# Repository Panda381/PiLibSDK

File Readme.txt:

PiLibSDK - Raspberry Pi bare-metal SDK library
==============================================
Pre-alpha version 0.46, in progress - under development
Last update: 08/05/2026

Copyright (c) 2026 Miroslav Nemecek

Panda38@seznam.cz
hardyplotter2@gmail.com
https://github.com/Panda381/PiLibSDK
https://www.breatharian.eu/hw/pilibsdk/index_en.html

License
=======
All of my software creations are distributed under the Unlicense
https://spdx.org/licenses/Unlicense.html,
and my hardware creations under the CC0 license
https://creativecommons.org/publicdomain/zero/1.0/legalcode.en.
You are free to use, modify, and distribute them for any purpose without having
to credit me as the author. The exception is content derived from third-party
sources. These third-party components are not covered by my Unlicense or CC0
licenses, but rather by the original license terms of their authors. These
components are marked in the code, and when using them, you must comply with
the terms of the original licenses.

All of my source code and data are completely free to use for any purpose. The
exception is certain files derived from third-party sources - these are subject
to the original author's license. This includes most fonts, as well as portions
of source files taken from the Circle library and Linux code - these sections
are marked in the source files.

Most fonts in this library are not my creation. They were downloaded from the
internet from unknown sources, with unknown license terms of use. If you want
to use only strict licenses, do not use fonts from this library.

Intro
=====
PiLibSDK is a bare-metal library for Raspberry Pi modules. "Bare-metal" means
that programs run directly on the hardware without an operating system, they
are not controlled by the operating system, and they have full access to the
hardware. Raspberry Pi modules can thus be used in a similar way to microchips.
Another advantage is that the device is fully operational within 3 seconds of
powering on. Currently, the Raspberry Zero 1, Zero 2 W, Pi 2, and Pi 3 modules
are supported. Support for the Pi 4 and Pi 5 modules is very limited, and they
will likely not be supported in the future either, as their benefits for
bare-metal use are minimal.

Sample programs have been prepared for the BarePi modular microchip kit.
(links: https://www.breatharian.eu/hw/barepi/index_en.html,
https://github.com/Panda381/BarePi). Of course, you don't have to follow the
hardware wiring exactly, but this is the most common pin-to-signal mapping.
The main device is the ZeroTiny game console, which corresponds to the
configuration of the "Zero," "Base," and "KeyPad" modules.

An LCD SPI display with a resolution of 320x240 pixels and ST7789 controller
can also be connected to the device. The wiring corresponds to the
"LCD320x240" module from the BarePi kit. The software library is designed so
that when it detects the connection of the LCD320x240 module, it activates the
SPI output to the display and sends the image to this LCD display as well.
Detection is performed using a 10K resistor connected between the DC and CS
pins. If you want to be able to disable the LCD display output on the target
device, you can do so using a switch that connects this 10K resistor. Detection
occurs when the application or loader starts - so after changing the switch,
you must terminate or start the program or loader. Disabling the output to the
LCD display ensures faster program execution, as sending data to the LCD
display heavily loads the program.

Although the LCD SPI display has a resolution of only 320x240 pixels, it is
possible to use programs with a resolution of 640x480 pixels. The driver
automatically scales the image down to the target size. If you need to display
details on the LCD display that would be lost due to the scaling, you can do so
by pressing Alt+[A] - the "Insert" function is used here to mean "Zoom". When
you press the keys, the LCD display will sequentially show each of the four
quadrants of the image in full resolution; pressing the keys a fifth time
restores the full scaled-down image.

If you do not need the HDMI output while using the LCD display, disconnect the
monitor cable. This will result in a significant reduction in current
consumption (from approximately 400 mA to 200 mA), which is especially
important when running the console on battery power. The system detects whether
an HDMI monitor is connected when the program starts - therefore, after
disconnecting or connecting an HDMI monitor, you must exit or restart the
program or loader. With the Raspberry Zero 1 module, it may be necessary to
disconnect and reconnect the power supply to detect the HDMI monitor.

If you connect a DS3231 real-time clock circuit to the device, applications
will retrieve the current real-time clock value from it. The I2C EEPROM memory
provides the ability to save program configurations.

A boot loader is available for BarePi devices, which allows easy launching of
programs from an SD card. The programs are ready for BarePi and ZeroTiny with
Zero 1, Zero 2 32-bit, or Zero 2 64-bit modules. The Zero 1 and Zero 2 modules
differ primarily in speed - the Zero 2 is noticeably faster than the Zero 1.
The higher speed is due not only to a higher processor frequency but also to a
newer architecture. In addition, the Zero 2 module has 4 cores, while the
Zero 1 has only one core. Therefore, it is strongly recommended to use the
Zero 2 module. Use the Zero 1 module only if you own it and have no better use
for it. The Zero 2 module can be operated in 32-bit or 64-bit mode. 64-bit mode
is faster. The compilations are prepared for both modes. From a user's point of
view, there is no noticeable difference between the modes. It is recommended to
prefer 64-bit mode, which may be slightly faster in some cases.

The BarePi kit can be controlled using either the "KeyPad" gaming keyboard or
the "MiniKey" alphanumeric keyboard. The keys on the "KeyPad" keyboard are also
mapped to the keys on the "MiniKey" keyboard. To distinguish between key
labels, action keys from the gaming keyboard are listed in square brackets,
while character keys are listed without brackets. For example, "[A]" denotes
the "A" action key on the gaming keyboard. The meanings of the keys on the
gaming keyboard and their mapping to the alphanumeric keyboard are as follows.

[A] = Space ... Main action button
[B] = Enter ... Secondary action button
[X] = Tab ... Auxiliary button, e.g. Help
[Y] = Esc ... Exit the menu, close the program
Alt+Left = Home ... Jump to start
Alt+Right = End ... Jump to end
Alt+Up = PgUp ... Page up
Alt+Down = PgDn ... Page down
Alt+A = Insert ... Insert mode (on LCD display, the "Zoom" function)
Alt+B = Edit ... Edit mode
Alt+X = PrtScr ... Take a screenshot and save it to an SD card
Alt+Y = Menu ... Call system menu

Note: A boot loader is not required to run programs. You can run programs
directly on the Zero1/Zero2 module itself, without additional hardware or a
boot loader. Copy the system files from the Root directory of the corresponding
!BarePi* folder to the SD card. You will need the files "bootcode.bin",
"config.txt", "fixup.dat", and "start.elf". Copy the program to the Root folder
as well, and rename it to KERNEL.IMG. The program will start automatically when
power is turned on.

Compilation
===========
To compile 32-bit mode, you will need AArch32 GCC
(tool name "arm-none-eabi"). Install to C:\ARM_GCC32.
https://developer.arm.com/-/media/Files/downloads/gnu/15.2.rel1/binrel/arm-gnu-toolchain-15.2.rel1-mingw-w64-i686-arm-none-eabi.msi

To compile 64-bit mode, you will need AArch64 GCC
(tool name "aarch64-none-elf"). Install to C:\ARM_GCC64.
 https://developer.arm.com/-/media/Files/downloads/gnu/15.2.rel1/binrel/arm-gnu-toolchain-15.2.rel1-mingw-w64-i686-aarch64-none-elf.msi
from https://developer.arm.com/downloads/-/arm-gnu-toolchain-downloads

If you will use another paths, edit paths in _c1.bat (set GCC_PI_PATH).

Directories
===========
!BarePi ... content of SD card for kit BarePi and ZeroTiny - common files
!BarePi_1 ... content of SD card for kit BarePi and ZeroTiny - executables for module Zero 1
!BarePi_3 ... content of SD card for kit BarePi and ZeroTiny - executables for module Zero 2 32-bit
!BarePi_4 ... content of SD card for kit BarePi and ZeroTiny - executables for module Zero 2 64-bit
_devices ... devices: BarePi = modular microchip kit and ZeroTiny device
_drv ... drivers
_font ... fonts
_lib ... libraries
_sdk ... SDK (peripheral controllers)
_tools ... compilation tools
Apps ... source codes of sample applications

To prepare the SD card, format it to FAT32, copy the contents of the !BarePi
folder to it, as well as one of the !BarePi_* folder (depending on the module
type).

Order of includes:

-> project "include.h"
   -> root "includes.h" (INCLUDES_H)
       -> root "global.h"
          -> project "config.h"
             -> root "config_def.h" (CONFIG_DEF_H)
                -> (called from start of config_def.h) device "_devices/barepi/_config.h"
       -> fonts "_font/_include.h"
       -> SDK "_sdk/_include.h"
       -> drivers "_drv/_include.h"
       -> LIB "_lib/_include.h"
       -> device "_devices/barepi/_include.h"

ZeroTiny
========
ZeroTiny is the simplest game console based on the Raspberry Pi Zero 1 or
Zero 2 modules. This corresponds to the assembly of the "Zero," "Base," and
"KeyPad" modules from the BarePi kit. It is recommended to preferably use the
Zero 2 module in 64-bit mode. The Zero 1 module may be noticeably slower in
some applications. ZeroTiny features 9 buttons, a stereo PWM audio output, and
an HDMI display output. A boot loader is available, allowing for easy program
launch from an SD card.

The ZeroTiny is designed in a sandwich-style construction. In my prototype,
I connected the Zero module to the motherboard via an 8mm header - primarily to
facilitate easy module replacement. If you solder the Zero module to the board
using only a pin header, the design will be lower. However, this may make
repairs more difficult, such as replacing a button.

Detailed materials for ZeroTiny hardware can be found in the
"_devices/BarePi/ZeroTiny" folder.

Source code and sample programs can be found in the "Apps" folder.

You can find the compiled sample programs in the "!BarePi*" folders,
organized by module type and processor mode.

Sample Applications
===================
System
 KERNEL ... Loader of applications
 SYSINFO ... System information

Book
 ABC ... Fairy Tales from the Alphabet (Czech)
 GINGER ... Gingerbread House (English)
 GINGERCZ ... Gingerbread House (Czech)

Demo
 BALLOONS ... Flying balloons
 BIGFACT ... Factorial of 123456789!
 DRAW ... Drawing graphic elements
 EARTH ... Rotating globe
 FLAG ... Fluttering flag
 FLAG2 ... Fluttering custom flag
 FOUNTAIN ... Draw 3D graph
 FRUITY .... 130 music loops with MP3 compression
 HELLO ... Simplest example
 HYPNO ... hypnotic rotating pattern
 LEVMETER ... simulation of music spectrum indicator
 LINEART ... draw line flower
 LINES ... relaxation line pattern generator
 MATRIX ... matrix code rain
 OSCIL ... simulation of oscilloscope signal 
 PF2027 ... Christmas animation
 PI ... calculating number Pi to 4780 digits
 PIXELS ... random generation of colored pixels
 RAYTRACE ... 3D pattern generation by ray tracing method
 SPHERES ... random spheres
 SPOTS ... random spots
 TWISTER ... twisting textured block
 WATER ... simulation of rippling water surface

Games
 ANTS ... Card game
 ATOMS ... Game of exploding atoms
 EGGS ... Logic game as Reversi
 FIFTEEN ... Logic puzzle game
 FLAPPY ... Logic game from Sharp MZ800
 CHESS ... Chess game
 INVADERS ... Shooting game Space Invaders
 LIFE ... Cell life simulator
 MAZE ... Find way out of maze
 PACMAN ... Action game Pac-Man
 PICTOR ... Picopad Collector
 RAPTOR ... Shooting game
 SOKOBAN ... Logic game, 3008 levels
 TETRIS ... Game stacking blocks
 TRAIN ... Logic game, 50 levels
 TVTENNIS ... Classic TV game
 VEGASLOT ... Winning Slot Machine
 ZOOM ... Buck Rogers-Planet of Zoom

MP3
 MP3 ... MP3 player

Program
 MANDELBROT ... Fast fractal pattern generator
   Demo fractal video on YouTube: https://www.youtube.com/watch?v=IikX4hZGXIg
   Source codes of the fractal generator on GitHub:
	https://github.com/Panda381/PiLibSDK/tree/main/Apps/PROGRAM/MANDEL/src

Test
 CALCKEY ... Test CalcKey keyboard
 EEPROM ... View contents of I2C EEPROMs
 I2CSCAN ... Scan I2C0 and I2C1 bus
 LCD ... Test LCD SPI display
 LCD16X2 ... Test LCD16x2 text display
 LED12 ... Test LED12 display
 MINIKEY ... Test MiniKey keyboard
 PORT12 ... Test PORT12 module
 RTC ... Display and set current time, using RTC module
 SSD1306 ... Test SSD1306 display
 TESTLED ... Test BarePi bus with TESTLED module

TinyGames
 TARKAN .. Tiny Arkanoid
 TBERT ... Tiny Bert
 TBIKE ... Tiny Bike
 TBOMBER ... Tiny Bomber
 TDDUG ... Tiny DDug
 TDOC ... Tiny Doctor
 TDUNGEON ... Tiny Dungeon
 TINVADER ... Tiny Invaders
 TMISSILE ... Tiny Missile
 TMORPION ... Tiny Morpion
 TPIPE ... Tiny Pipe
 TPLAQUE ... Tiny Plaque
 TSQUEST ... Tiny SQuest
 TTRICK ... Tiny Trick
 TTRIS ... Tiny Tris

----------------

Notes:

Raspberry Zero 2 W contains:
- PAM2306AYPKE dual PWM step-down DC-DC converter, input 2.5 to 5V, output 3.3V and 1.8V, current 1A
- RT8088AWSC 2.7MHz 3A Step-Down Converter with I2C Interface
- RP3A0 SiP (BCM2710A1 + 512 MB SDRAM LPDDR2), quartz 19.2 MHz
- RT9081A-1BGQZA(2) Richtek LDO Voltage Regulators 500mA 5.5V, input 3.3V, output DDR 1.25V

UART

To connect Pi to PC via serial port, you need convertor
to USB port. Good choise is USB-serial adaptor PL2303TA.

   How to connect UART to Pi:

                    +---------+
                3V3 |.1     2.| 5V
              GPIO2 |.3     4.| 5V
              GPIO3 |.5     6.| GND  ----> connect to (black) GND of PL2303
              GPIO4 |.7     8.| GPIO14 - TXD ----> connect to (white) RxD of PL2303
                GND |.9    10.| GPIO15 - RXD
                      ......

	Do not connect +5V (red) from PL2303
	Do not connect TXD from PL2303 (green), it can have 5V level.

   You need console program (as PuTTY) to see demo text.
   Setup port to 115200 Baud, 8 bits, 1 stop bit, no parity,
   flow control None.

   In Device Manager, USB adaptor can be found under name:
           "Prolific USB-to-Serial Comm Port (COM10)".

Exporting a TGA image with transparency, using Photoshop:

- Select / Load Selection, Channel = Layer 0 Transparency (do not check Invert)
- Select / Save Selection, Channel = New (Name can remain blank, Alpha 1 will be used)
- Save As, switch to TGA, "Alpha Channels" must be checked, resolution 32 bits/pixel

Importing a TGA image with transparency, using Photoshop:

- Open and load TGA
- Layer / New / Layer from Background
- Select / Load Selection, Channel = Alpha 1 (do not check Invert)
- Layer / Layer Mask / Reveal Selection
- Layer / Layer Mask / Apply
- In Channels, select the Alpha 1 channel and cancel it

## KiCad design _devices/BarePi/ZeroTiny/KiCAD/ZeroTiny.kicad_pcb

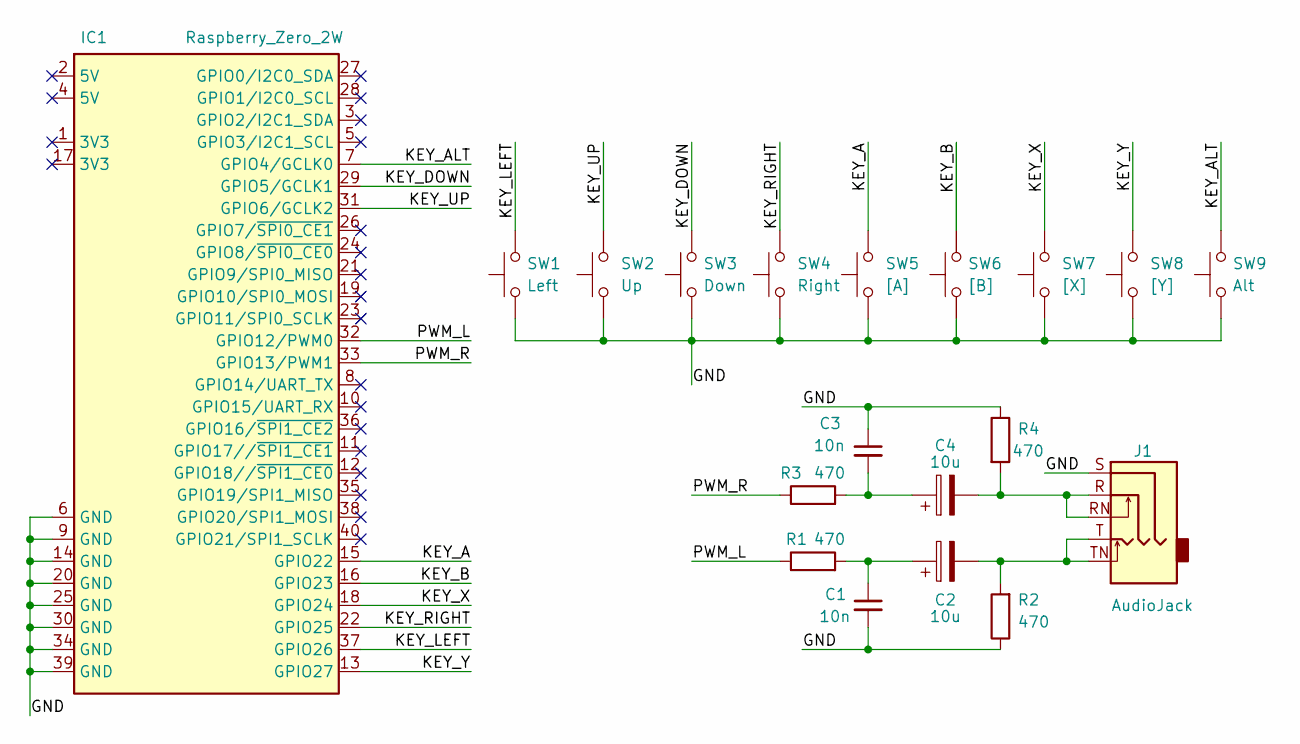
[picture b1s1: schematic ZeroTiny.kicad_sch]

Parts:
C1, C3: 10n; C_1206_3216Metric_Pad1.33x1.80mm_HandSolder
C2, C4: 10u; CP_EIA-3528-21_Kemet-B_HandSolder
IC1: Raspberry_Zero_2W; Raspberry_Pi_Zero_Socketed_THT_FaceDown_MountingHoles
J1: AudioJack; Jack_3.5mm_CUI_SJ1-3515N_Horizontal
R1, R2, R3, R4: 470; R_1206_3216Metric_Pad1.30x1.75mm_HandSolder
SW1: Left; SW_PUSH_6mm
SW2: Up; SW_PUSH_6mm
SW3: Down; SW_PUSH_6mm
SW4: Right; SW_PUSH_6mm
SW5: [A]; SW_PUSH_6mm
SW6: [B]; SW_PUSH_6mm
SW7: [X]; SW_PUSH_6mm
SW8: [Y]; SW_PUSH_6mm
SW9: Alt; SW_PUSH_6mm

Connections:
/GND: C1.2, C3.1, IC1.6 (GND), IC1.9 (GND), IC1.14 (GND), IC1.20 (GND), IC1.25 (GND), IC1.30 (GND), IC1.34 (GND), IC1.39 (GND), J1.S, R2.1, R4.1, SW1.1, SW2.1, SW3.1, SW4.1, SW5.1, SW6.1, SW7.1, SW8.1, SW9.1
/KEY_A: IC1.15 (GPIO22), SW5.2
/KEY_ALT: IC1.7 (GPIO4/GCLK0), SW9.2
/KEY_B: IC1.16 (GPIO23), SW6.2
/KEY_DOWN: IC1.29 (GPIO5/GCLK1), SW3.2
/KEY_LEFT: IC1.37 (GPIO26), SW1.2
/KEY_RIGHT: IC1.22 (GPIO25), SW4.2
/KEY_UP: IC1.31 (GPIO6/GCLK2), SW2.2
/KEY_X: IC1.18 (GPIO24), SW7.2
/KEY_Y: IC1.13 (GPIO27), SW8.2
/PWM_L: IC1.32 (GPIO12/PWM0), R1.1
/PWM_R: IC1.33 (GPIO13/PWM1), R3.1
unnamed: C1.1, C2.1, R1.2
unnamed: C2.2, J1.T, J1.TN, R2.2
unnamed: C3.2, C4.1, R3.2
unnamed: C4.2, J1.R, J1.RN, R4.2

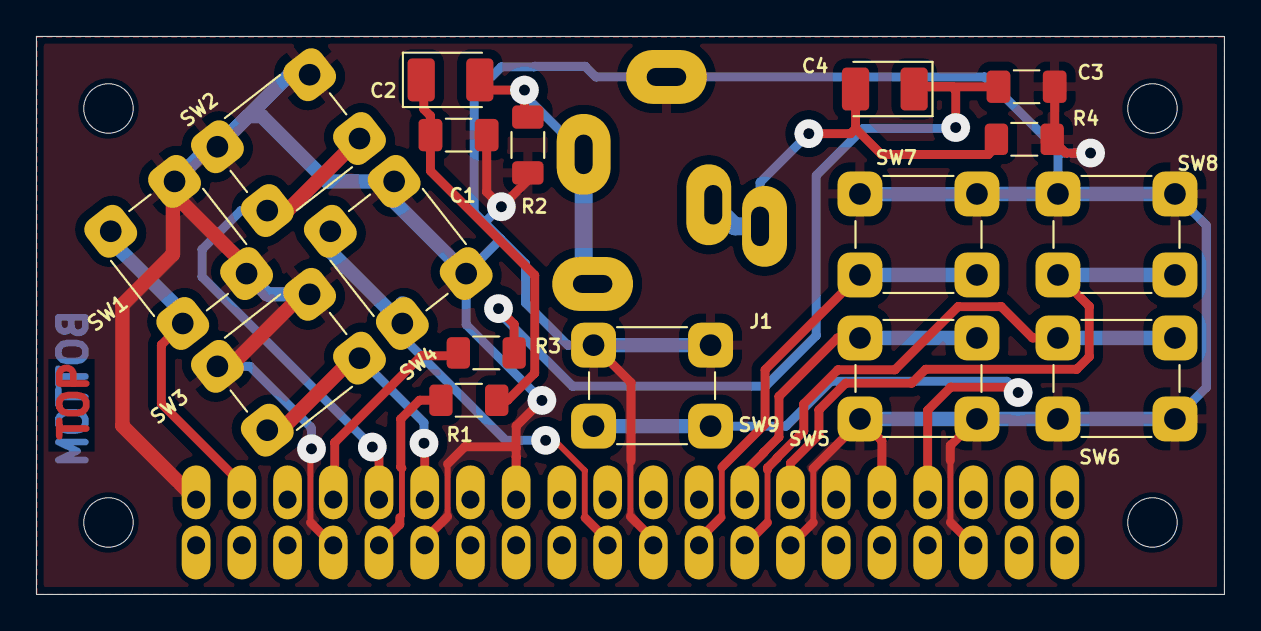
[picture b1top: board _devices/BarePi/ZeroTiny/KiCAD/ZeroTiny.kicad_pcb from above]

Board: 2 copper layers, 66.0 x 31.0 mm, 19 parts (1 on the bottom side), 16 nets.

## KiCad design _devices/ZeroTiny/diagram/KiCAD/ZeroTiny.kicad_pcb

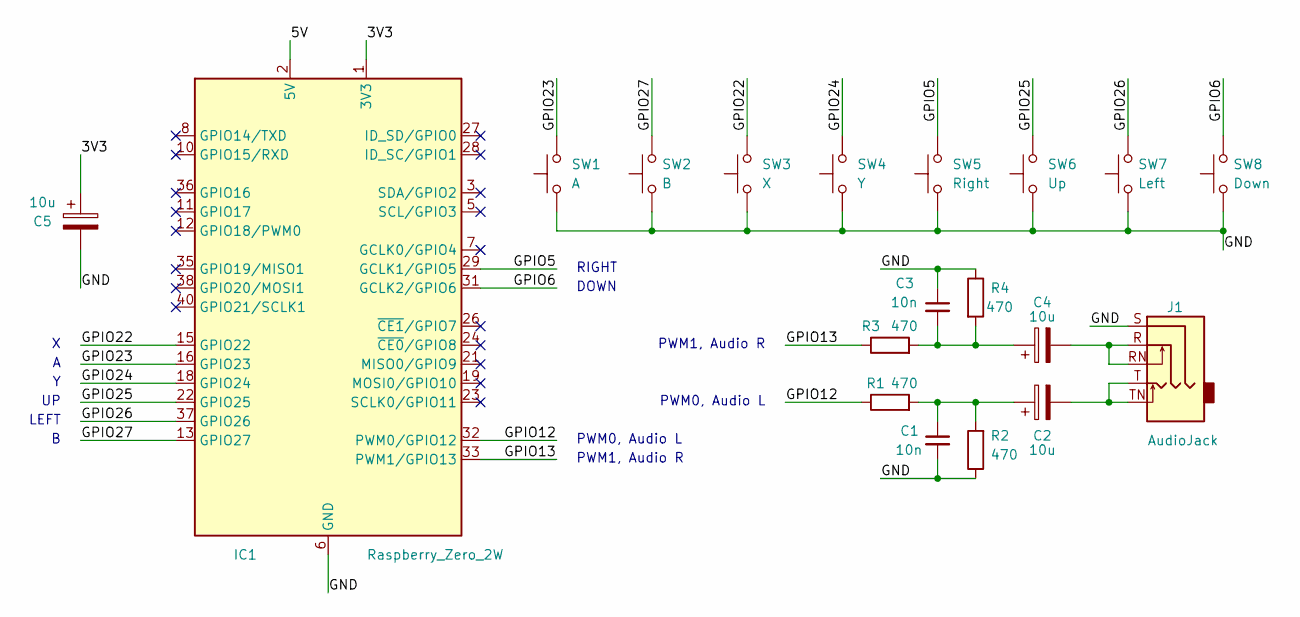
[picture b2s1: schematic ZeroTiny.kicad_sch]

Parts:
C1, C3: 10n; C_1210_3225Metric_Pad1.33x2.70mm_HandSolder
C2, C4, C5: 10u; CP_Elec_5x3
IC1: Raspberry_Zero_2W; Raspberry_Pi_Zero_Socketed_THT_FaceDown_MountingHoles
J1: AudioJack; Jack_3.5mm_CUI_SJ1-3515N_Horizontal
R1, R2, R3, R4: 470; R_1206_3216Metric_Pad1.30x1.75mm_HandSolder
SW1: A; SW_PUSH_6mm
SW2: B; SW_PUSH_6mm
SW3: X; SW_PUSH_6mm
SW4: Y; SW_PUSH_6mm
SW5: Right; SW_PUSH_6mm
SW6: Up; SW_PUSH_6mm
SW7: Left; SW_PUSH_6mm
SW8: Down; SW_PUSH_6mm

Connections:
/3V3: C5.1, IC1.1 (3V3), IC1.17 (3V3)
/5V: IC1.2 (5V), IC1.4 (5V)
/GND: C1.2, C3.1, C5.2, IC1.6 (GND), IC1.9 (GND), IC1.14 (GND), IC1.20 (GND), IC1.25 (GND), IC1.30 (GND), IC1.34 (GND), IC1.39 (GND), J1.S, R2.1, R4.1, SW1.1, SW2.1, SW3.1, SW4.1, SW5.1, SW6.1, SW7.1, SW8.1
/GPIO5: IC1.29 (GCLK1/GPIO5), SW5.2
/GPIO6: IC1.31 (GCLK2/GPIO6), SW8.2
/GPIO12: IC1.32 (PWM0/GPIO12), R1.1
/GPIO13: IC1.33 (PWM1/GPIO13), R3.1
/GPIO22: IC1.15 (GPIO22), SW3.2
/GPIO23: IC1.16 (GPIO23), SW1.2
/GPIO24: IC1.18 (GPIO24), SW4.2
/GPIO25: IC1.22 (GPIO25), SW6.2
/GPIO26: IC1.37 (GPIO26), SW7.2
/GPIO27: IC1.13 (GPIO27), SW2.2
unnamed: C1.1, C2.1, R1.2, R2.2
unnamed: C2.2, J1.T, J1.TN
unnamed: C3.2, C4.1, R3.2, R4.2
unnamed: C4.2, J1.R, J1.RN

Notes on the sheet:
PWM1, Audio R
PWM0, Audio L
LEFT
RIGHT
DOWN

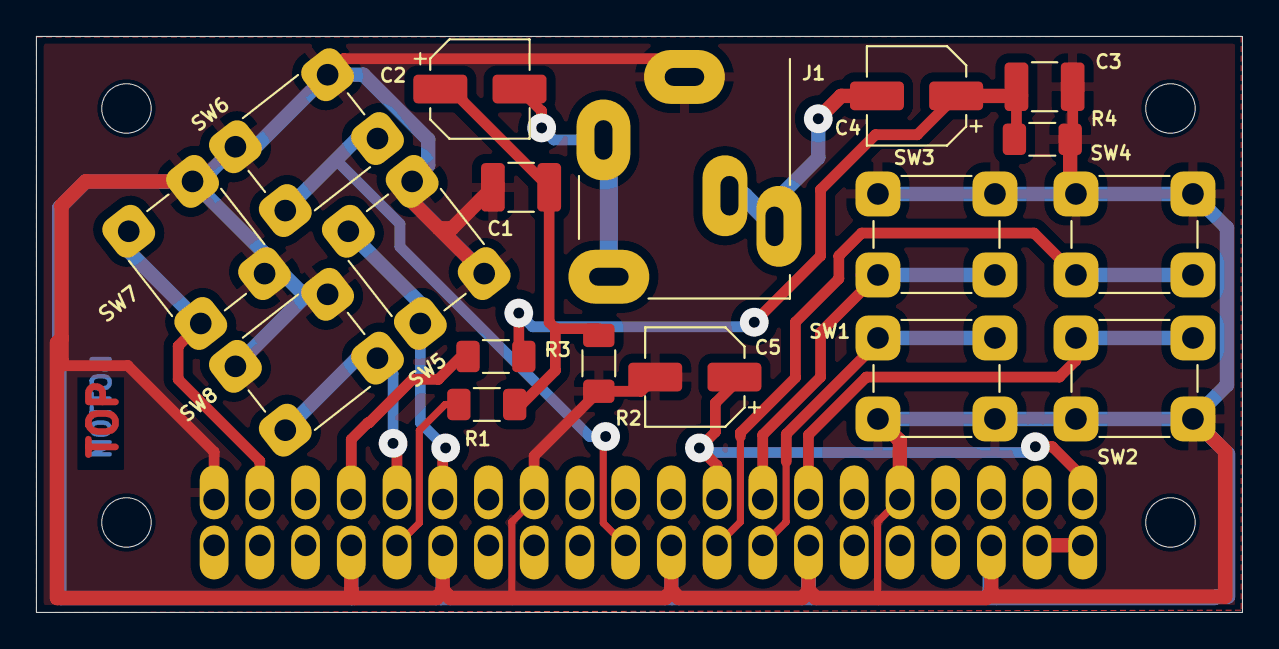
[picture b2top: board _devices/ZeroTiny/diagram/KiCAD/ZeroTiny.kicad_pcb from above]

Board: 2 copper layers, 67.0 x 32.0 mm, 19 parts (1 on the bottom side), 17 nets.

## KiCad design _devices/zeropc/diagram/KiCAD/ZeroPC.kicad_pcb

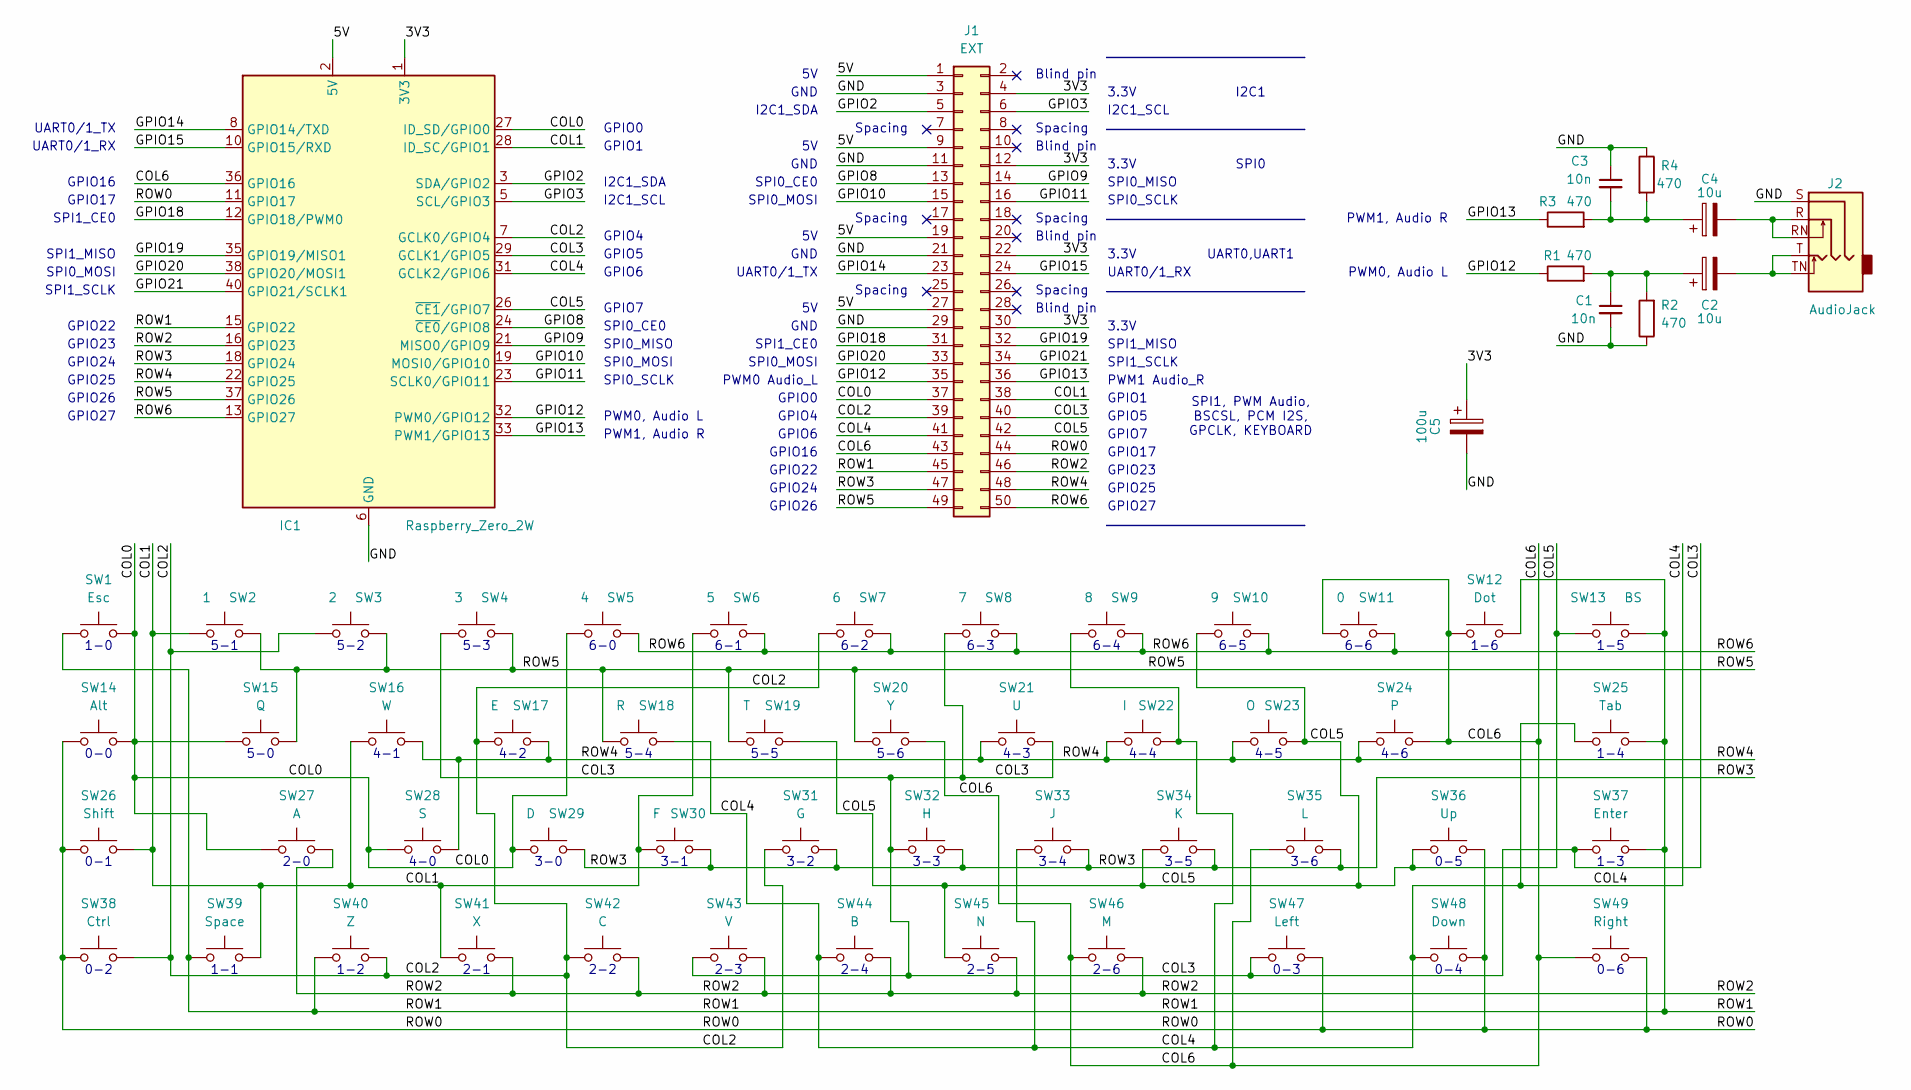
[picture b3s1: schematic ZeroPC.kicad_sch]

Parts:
C1, C3: 10n; C_Axial_L3.8mm_D2.6mm_P10.00mm_Horizontal
C2, C4: 10u; CP_Radial_D5.0mm_P2.50mm
C5: 100u; CP_Radial_D5.0mm_P2.50mm
IC1: Raspberry_Zero_2W; Raspberry_Pi_Zero_Socketed_THT_FaceDown_MountingHoles
J1: EXT; IDC-Header_2x25_P2.54mm_Horizontal
J2: AudioJack; Jack_3.5mm_CUI_SJ1-3515N_Horizontal
R1, R2, R3, R4: 470; R_Axial_DIN0207_L6.3mm_D2.5mm_P10.16mm_Horizontal
SW1: Esc; SW_PUSH_6mm
SW2: 1; SW_PUSH_6mm
SW3: 2; SW_PUSH_6mm
SW4: 3; SW_PUSH_6mm
SW5: 4; SW_PUSH_6mm
SW6: 5; SW_PUSH_6mm
SW7: 6; SW_PUSH_6mm
SW8: 7; SW_PUSH_6mm
SW9: 8; SW_PUSH_6mm
SW10: 9; SW_PUSH_6mm
SW11: 0; SW_PUSH_6mm
SW12: Dot; SW_PUSH_6mm
SW13: BS; SW_PUSH_6mm
SW14: Alt; SW_PUSH_6mm
SW15: Q; SW_PUSH_6mm
SW16: W; SW_PUSH_6mm
SW17: E; SW_PUSH_6mm
SW18: R; SW_PUSH_6mm
SW19: T; SW_PUSH_6mm
SW20: Y; SW_PUSH_6mm
SW21: U; SW_PUSH_6mm
SW22: I; SW_PUSH_6mm
SW23: O; SW_PUSH_6mm
SW24: P; SW_PUSH_6mm
SW25: Tab; SW_PUSH_6mm
SW26: Shift; SW_PUSH_6mm
SW27: A; SW_PUSH_6mm
SW28: S; SW_PUSH_6mm
SW29: D; SW_PUSH_6mm
SW30: F; SW_PUSH_6mm
SW31: G; SW_PUSH_6mm
SW32: H; SW_PUSH_6mm
SW33: J; SW_PUSH_6mm
SW34: K; SW_PUSH_6mm
SW35: L; SW_PUSH_6mm
SW36: Up; SW_PUSH_6mm
SW37: Enter; SW_PUSH_6mm
SW38: Ctrl; SW_PUSH_6mm
SW39: Space; SW_PUSH_6mm
SW40: Z; SW_PUSH_6mm
SW41: X; SW_PUSH_6mm
SW42: C; SW_PUSH_6mm
SW43: V; SW_PUSH_6mm
SW44: B; SW_PUSH_6mm
SW45: N; SW_PUSH_6mm
SW46: M; SW_PUSH_6mm
SW47: Left; SW_PUSH_6mm
SW48: Down; SW_PUSH_6mm
SW49: Right; SW_PUSH_6mm

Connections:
/3V3: C5.1, IC1.1 (3V3), IC1.17 (3V3), J1.4, J1.12, J1.22, J1.30
/5V: IC1.2 (5V), IC1.4 (5V), J1.1, J1.9, J1.19, J1.27
/COL0: IC1.27 (ID_SD/GPIO0), J1.37, SW1.2, SW5.1, SW14.2, SW15.1, SW27.1, SW28.1, SW29.1
/COL1: IC1.28 (ID_SC/GPIO1), J1.38, SW2.1, SW6.1, SW16.1, SW26.2, SW30.1, SW39.2, SW41.1
/COL2: IC1.7 (GCLK0/GPIO4), J1.39, SW3.1, SW7.1, SW17.1, SW31.1, SW38.2, SW40.2, SW42.1
/COL3: IC1.29 (GCLK1/GPIO5), J1.40, SW4.1, SW8.1, SW21.2, SW32.1, SW37.1, SW43.1, SW47.1
/COL4: IC1.31 (GCLK2/GPIO6), J1.41, SW9.1, SW18.2, SW22.2, SW25.1, SW33.1, SW44.1, SW48.1
/COL5: IC1.26 (~CE1/GPIO7), J1.42, SW10.1, SW13.1, SW19.2, SW23.2, SW34.1, SW36.1, SW45.1
/COL6: IC1.36 (GPIO16), J1.43, SW11.1, SW12.1, SW20.2, SW24.2, SW35.1, SW46.1, SW49.1
/GND: C1.2, C3.1, C5.2, IC1.6 (GND), IC1.9 (GND), IC1.14 (GND), IC1.20 (GND), IC1.25 (GND), IC1.30 (GND), IC1.34 (GND), IC1.39 (GND), J1.3, J1.11, J1.21, J1.29, J2.S, R2.1, R4.1
/GPIO2: IC1.3 (SDA/GPIO2), J1.5
/GPIO3: IC1.5 (SCL/GPIO3), J1.6
/GPIO8: IC1.24 (~CE0/GPIO8), J1.13
/GPIO9: IC1.21 (MISO0/GPIO9), J1.14
/GPIO10: IC1.19 (MOSI0/GPIO10), J1.15
/GPIO11: IC1.23 (SCLK0/GPIO11), J1.16
/GPIO12: IC1.32 (PWM0/GPIO12), J1.35, R1.1
/GPIO13: IC1.33 (PWM1/GPIO13), J1.36, R3.1
/GPIO14: IC1.8 (GPIO14/TXD), J1.23
/GPIO15: IC1.10 (GPIO15/RXD), J1.24
/GPIO18: IC1.12 (GPIO18/PWM0), J1.31
/GPIO19: IC1.35 (GPIO19/MISO1), J1.32
/GPIO20: IC1.38 (GPIO20/MOSI1), J1.33
/GPIO21: IC1.40 (GPIO21/SCLK1), J1.34
/ROW0: IC1.11 (GPIO17), J1.44, SW14.1, SW26.1, SW36.2, SW38.1, SW47.2, SW48.2, SW49.2
/ROW1: IC1.15 (GPIO22), J1.45, SW1.1, SW12.2, SW13.2, SW25.2, SW37.2, SW39.1, SW40.1
/ROW2: IC1.16 (GPIO23), J1.46, SW27.2, SW41.2, SW42.2, SW43.2, SW44.2, SW45.2, SW46.2
/ROW3: IC1.18 (GPIO24), J1.47, SW29.2, SW30.2, SW31.2, SW32.2, SW33.2, SW34.2, SW35.2
/ROW4: IC1.22 (GPIO25), J1.48, SW16.2, SW17.2, SW21.1, SW22.1, SW23.1, SW24.1, SW28.2
/ROW5: IC1.37 (GPIO26), J1.49, SW2.2, SW3.2, SW4.2, SW15.2, SW18.1, SW19.1, SW20.1
/ROW6: IC1.13 (GPIO27), J1.50, SW5.2, SW6.2, SW7.2, SW8.2, SW9.2, SW10.2, SW11.2
unnamed: C1.1, C2.1, R1.2, R2.2
unnamed: C2.2, J2.T, J2.TN
unnamed: C3.2, C4.1, R3.2, R4.2
unnamed: C4.2, J2.R, J2.RN

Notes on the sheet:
GPIO26
SPI0_SCLK
3-0
1-2
Spacing
SPI0_CE0
SPI0_MOSI
2-0
5-0
UART0/1_RX
3-5
PWM1, Audio R
3.3V
GPIO5
0-5
GPIO4
GPIO25
SPI1_SCLK
1-4
SPI1_CE0
I2C1_SDA
3-6
0-4
3-1
GPIO17
PWM0, Audio L
UART0,UART1
SPI0_MISO
6-0
6-2
UART0/1_TX
2-5
4-1
2-3
5-6
GPIO0
GPIO22
SPI1_MISO
5-1
1-5

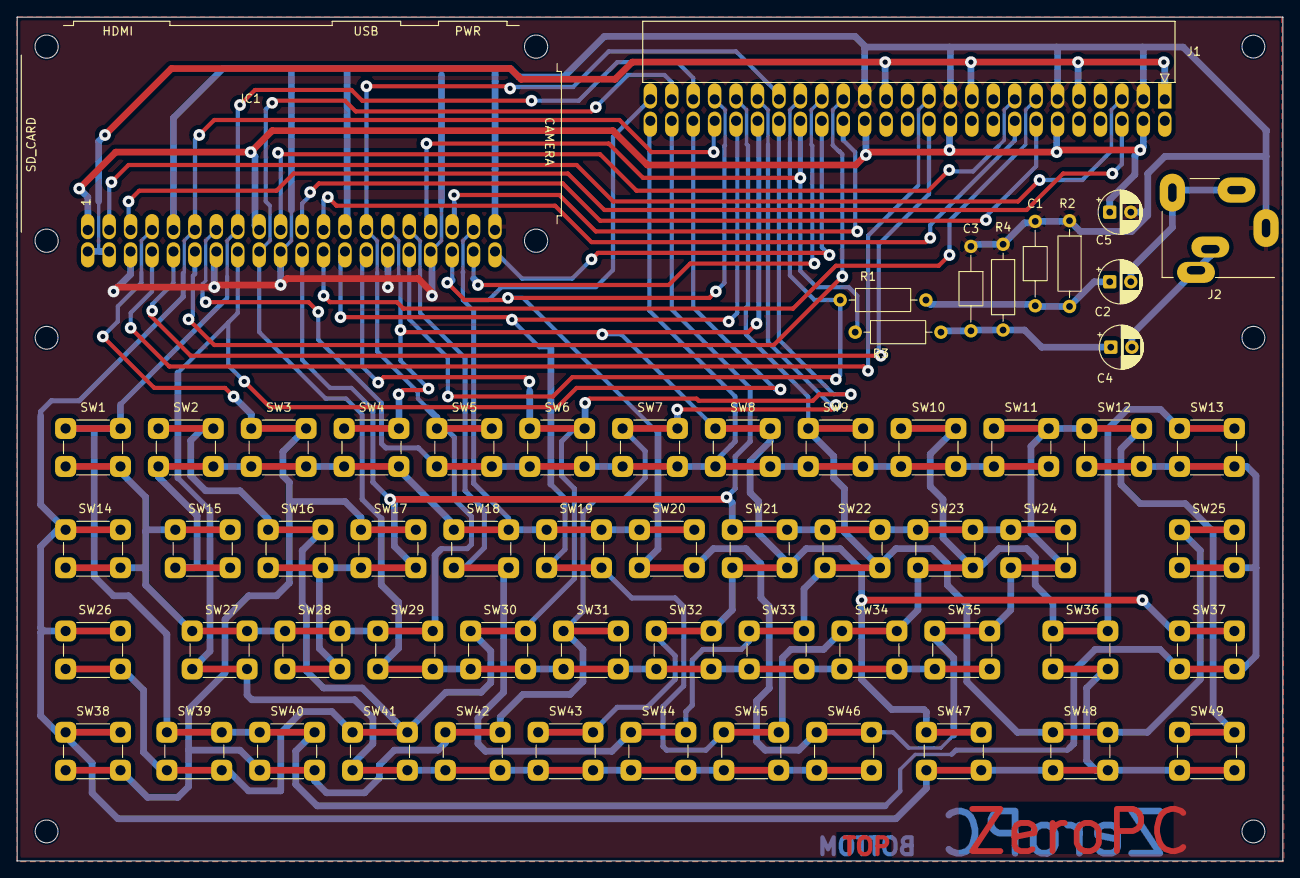
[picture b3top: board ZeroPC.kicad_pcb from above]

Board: 2 copper layers, 150.0 x 100.0 mm, 61 parts (0 on the bottom side), 35 nets.

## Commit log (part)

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2026-03-21 init
